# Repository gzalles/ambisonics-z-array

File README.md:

# MEMS Z-Array Mics

## [WIKI](https://github.com/gzalles/ambisonics-z-array/wiki)

A family of ambisonic microphones designed with MEMS capsules. These are affordable, easy-to-build arrays which can be used for multichannel audio recording (i.e., ambisonics).

Find an updated list of associated assets here:

1. m: Octave GNU code for plotting, analyzing and calibrating yourr own array
2. cad: various 3d objects you can print either online or at your university.
3. pcb: the files you need to make the pcbs or also you can have them made elsewhere.
4. svg: laser cutting files
5. conf: configuration files for kronlachner's convolution plug-in and filters
6. json: encoder presets for IEM MatrixMultiplier
7. wiki: instructions to build arrays

[AES Paper 1](https://www.researchgate.net/publication/320188555_A_Low-Cost_High-Quality_MEMS_Ambisonic_Microphone)

[AES Paper 2](https://www.researchgate.net/publication/338123588_Effects_of_Capsule_Coincidence_in_FOA_using_MEMS_Objective_Experiment)

<!-- TODO: move links to site.
 -->

## Pictures

<p align="center">
  
  <figcaption>

BigSpHEAR by FLL (working on a permutation).

## Contributing

Feel free to fork and request merge if you are interested in the project. Email to gzalles at ucsd dot edu.

## Authors

* [**Gabriel Zalles Ballivian**](http://gabrielzalles.com/)

## License

This project is licensed under the MIT License - see the [LICENSE.md](LICENSE.md) file for details

## Acknowledgments

* Charles Middlicott
* Charlie Mydlarz
* Agnieszka Roginska
* Julian Vanesse
* Andrea Genovese
* Braxton Boren
* Fernando Lopez-Lezcano
* Julius O Smith
* Alex Tung (Qualcomm)
* Raimundi Gonzalez (MSMA)
* Spencer Capiello (NYU)

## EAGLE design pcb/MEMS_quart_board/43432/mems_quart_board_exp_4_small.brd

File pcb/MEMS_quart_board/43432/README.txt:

43432 I2S Mic 

[VDD from J3 pin 2 on MCH]

LEFT and RIGHT PCBs (separate)

Left = CH1
Right = Ch2

Left tied to GRN (SEL)
Right tied to VDD (SEL)

MCH
///

BCLK > SCK 
LRCLK > WS 

Each data line has 2 channels. 
//////////////////////////////
J1 #2 input = channels 1/2
J1 #4 input = channels 3/4
etc.

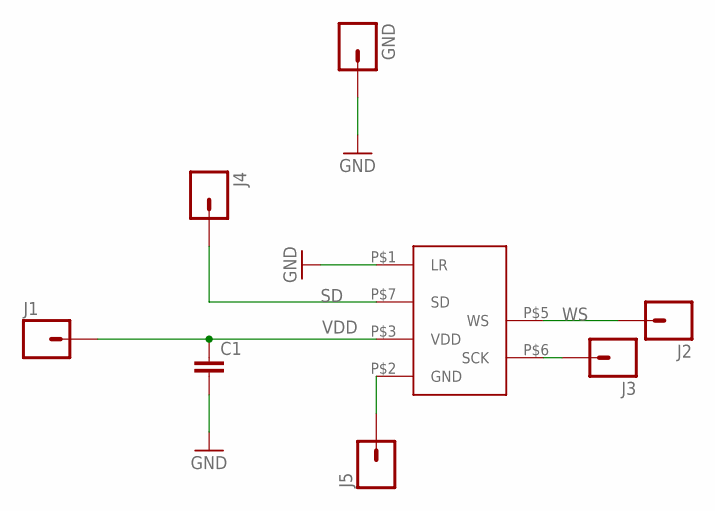
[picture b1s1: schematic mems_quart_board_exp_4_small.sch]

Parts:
C1: 0.1UF-16V(+-10%)(0402); 0402-CAP
GND: M01PTH_NO_SILK_YES_STOP; 1X01_NO_SILK
J1, J2, J3, J4, J5: M01NOSILK-KIT; 1X01NS-KIT
U$1: MEMS_ICS_43432

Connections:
GND: C1.2, GND.1, J5.1, U$1.P$1 (LR), U$1.P$2 (GND)
SCK: J3.1, U$1.P$6 (SCK)
SD: J4.1, U$1.P$7 (SD)
VDD: C1.1, J1.1, U$1.P$3 (VDD)
WS: J2.1, U$1.P$5 (WS)

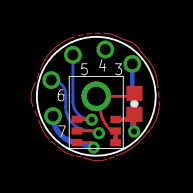
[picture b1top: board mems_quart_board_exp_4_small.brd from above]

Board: 2 copper layers, 6.6 x 6.6 mm, 8 parts (0 on the bottom side), 5 nets.

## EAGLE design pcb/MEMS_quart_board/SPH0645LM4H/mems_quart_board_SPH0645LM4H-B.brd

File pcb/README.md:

# PCB Files

* 3_175mmRadius: panelized files (can also be found in zip format)
* mems_quart_board_ics_40720.brd : single PCB for editing if needed.

These are the panelized files for the ICS-40720 board that Charlie Mydlarz designed. The radius of the board is 3.175mm. These are the current boards we are using for the analog mems FOA mic. I also added the original without panelizing.

There is a lot of information of the datasheet online regarding these capsules. In order to acquire these board one must find a PCB manufacturer and pay them to send you the boards.

In our current design we opt for 1mm thickness.

We use 2-sided PCBs.

If you need the dimensions of the board you can use: http://www.gerber-viewer.com/

The only thing they ask is to upload the zipped file. I have added the zipped file for your convenience since all sites as for it this way.

You might also want to get a stencil. With it you can more easily apply the paste to you PCBs.

credit: charlie mydlarz.

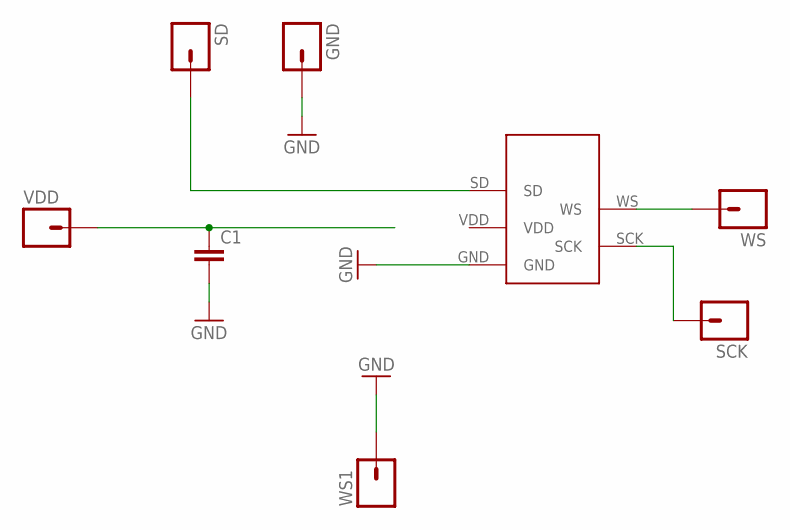
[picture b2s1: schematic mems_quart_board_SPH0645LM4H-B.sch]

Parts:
C1: 0.1UF-16V(+-10%)(0402); 0402-CAP
GND: M01PTH_NO_SILK_YES_STOP; 1X01_NO_SILK
SCK: M01NOSILK-KIT; 1X01NS-KIT
SD: M01NOSILK-KIT; 1X01NS-KIT
U$2: MEM_SPH0645LM4H-B; MEMS_SPH0645LM4H-B
VDD: M01NOSILK-KIT; 1X01NS-KIT
WS, WS1: M01NOSILK-KIT; 1X01NS-KIT

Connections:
GND: C1.2, GND.1, U$2.GND, WS1.1
unnamed: SCK.1, U$2.SCK
unnamed: SD.1, U$2.SD
unnamed: U$2.WS, WS.1
VDD: C1.1, U$2.VDD, VDD.1

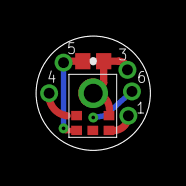
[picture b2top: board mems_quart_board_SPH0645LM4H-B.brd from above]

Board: 2 copper layers, 6.3 x 6.3 mm, 8 parts (0 on the bottom side), 5 nets.

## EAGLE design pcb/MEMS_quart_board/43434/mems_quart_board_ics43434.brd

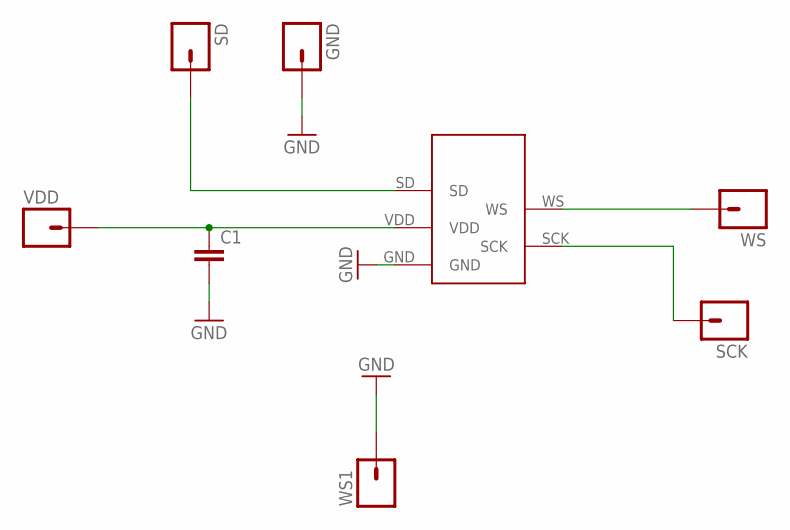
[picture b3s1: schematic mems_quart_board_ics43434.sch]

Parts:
C1: 0.1UF-16V(+-10%)(0402); 0402-CAP
GND: M01PTH_NO_SILK_YES_STOP; 1X01_NO_SILK
SCK: M01NOSILK-KIT; 1X01NS-KIT
SD: M01NOSILK-KIT; 1X01NS-KIT
U$1: MEM_ICS_43434; MEMS_ICS_43434
VDD: M01NOSILK-KIT; 1X01NS-KIT
WS, WS1: M01NOSILK-KIT; 1X01NS-KIT

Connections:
GND: C1.2, GND.1, U$1.GND, WS1.1
unnamed: SCK.1, U$1.SCK
unnamed: SD.1, U$1.SD
unnamed: U$1.WS, WS.1
VDD: C1.1, U$1.VDD, VDD.1

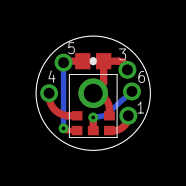
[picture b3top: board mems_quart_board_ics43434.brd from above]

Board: 2 copper layers, 6.3 x 6.3 mm, 8 parts (0 on the bottom side), 5 nets.

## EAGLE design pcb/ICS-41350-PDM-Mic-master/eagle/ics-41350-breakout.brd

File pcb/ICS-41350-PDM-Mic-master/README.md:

# ICS-41350-PDM-Mic
Open Source pcb layout and design for InvenSense ICS-41350 PDM Mic

# Datasheet
https://www.invensense.com/wp-content/uploads/2016/02/DS-000047-ICS-41350-v1.1.pdf

# Order PCBs
https://oshpark.com/shared_projects/o22Ddhzi

# Order ICS-41350
https://www.digikey.ca/product-detail/en/tdk-invensense/ICS-41350/1428-1064-1-ND/6025660

You'll also need a 0805 10uF and a 0603 .1uF smd capacitors and a 0603 10K Resistor.

# Front and Back PCB Preview

>The arrow points to where the hole for the mic goes.

>Bridge the S and G pad before using and bridge all three (S, G, V) if using module as RIGHT for stereo.

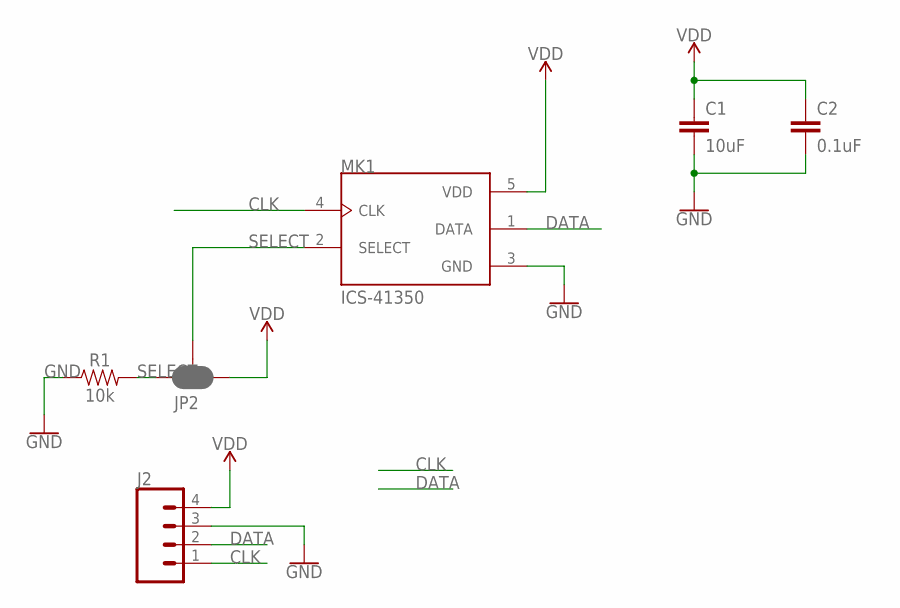
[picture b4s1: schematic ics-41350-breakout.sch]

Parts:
C1: 10uF; 0805
C2: 0.1uF; 0603
J2: CONN_041X04_NO_SILK; 1X04_NO_SILK
JP2: JUMPER-SMT_3_2-NC_PASTE_SILK; SMT-JUMPER_3_2-NC_PASTE_SILK
MK1: ICS-41350; MIC_ICS-41350
R1: 10k; 0603

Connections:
CLK: J2.1, MK1.4 (CLK)
DATA: J2.2, MK1.1 (DATA)
GND: C1.2, C2.2, J2.3, MK1.3 (GND), R1.1
SELECT: JP2.2, JP2.3, MK1.2 (SELECT), R1.2
VDD: C1.1, C2.1, J2.4, JP2.1, MK1.5 (VDD)

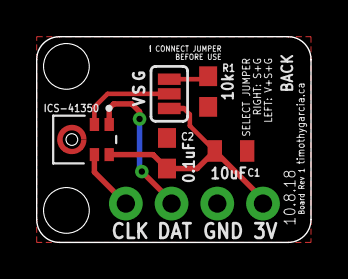
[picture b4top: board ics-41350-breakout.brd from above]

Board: 2 copper layers, 15.2 x 11.4 mm, 6 parts (0 on the bottom side), 5 nets.

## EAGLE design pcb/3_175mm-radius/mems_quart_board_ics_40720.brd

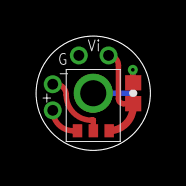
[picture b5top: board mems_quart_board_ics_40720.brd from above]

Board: 2 copper layers, 6.3 x 6.3 mm, 7 parts (0 on the bottom side), 4 nets.

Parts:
C1: 0402-CAP
GND: 1X01_NO_SILK
GND_IN: 1X01NS-KIT
U$1: MEMS_ICS_40720
VDD: 1X01NS-KIT
VOUT+: 1X01NS-KIT
VOUT-: 1X01NS-KIT

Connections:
GND: C1.2, GND.1, GND_IN.1, U$1.GND
VDD: C1.1, U$1.VDD, VDD.1
VOUT+: U$1.VOUT+, VOUT+.1
VOUT-: U$1.VOUT-, VOUT-.1

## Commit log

2019-04-18 push docs folder, try making site
2019-04-18 Set theme jekyll-theme-slate
2019-04-18 testing jekyll sites from doc folder
2019-04-18 read me and site, both readmes can be the same, but you have to do it manualy...
2019-04-19 Set theme jekyll-theme-cayman
2019-04-19 remove doc folder, oops
2019-04-19 added stuff from gsite and now have site building from amin branch (rather than docs)
2019-04-29 update materials on readme
2019-05-01 more added to the materials section
2019-05-01 testing pages
2019-05-01 still testing pages, relative path?
2019-05-01 push page 2
2019-05-01 testing page2 1:27
2019-05-03 push image 1
2019-05-03 this is a message
2019-05-03 from relative path to the other kind
    what is the other one?
2019-05-03 case sensitive
2019-05-03 commit for safety
2019-05-03 not sure what this is but it is bothering me so whatver
2019-05-03 back to relative with string uper case
2019-05-03 arrows on pic and stuff
2019-05-03 weird
2019-05-03 bob with arrow
2019-05-03 commit new image
2019-05-03 align the image? smaller?
2019-05-03 resize the other way
2019-05-03 old image is new
2019-05-03 get rid of old bob with arrows. DS_store thing?
2019-05-03 using % now for image size, better
2019-05-03 more materials links etc.
2019-05-03 little discrepancy fix with list
2019-05-03 problem persists
2019-05-04 matlab readme
2019-05-04 pushing readme modifications and gerzon filter. also stepper test. I want to write on the paper the methodology I used for getting my impulse response measurements. it would also be a goog idea to se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
2019-05-04 more instructions and links in the materials
2019-05-04 for some reason the image did not get uploaded...
2019-05-04 list numbering bug fix attempt
2019-05-04 bug list numbering fix 2
2019-05-04 how does the new pic look online?
2019-05-04 zipped gerber files, panelized
2019-05-05 the obj files looked all blurry stl seem to be better
2019-05-05 image to cad folder and a bit of info on the alligator mic clip;
2019-05-05 push the image itself
2019-05-05 link to paper and other details
2019-05-05 path change on cad image
2019-05-05 testing pages cad folder link?
2019-05-05 the pages thing worked!
2019-08-29 update gitignore
2019-08-29 wiki added
2019-08-29 wiki recursion avoided
2020-01-15 reset
2020-01-15 moving images to the wiki
2020-01-15 move img to wiki, master bracnh
2020-01-15 new readme, moved everything to wiki
2020-01-16 processing
2020-01-16 add audio and mat folder
2020-06-26 ud rm
2020-10-08 links to papers via researchgate
    🎤
2020-10-08 formatting issue
    is it fixed?
2020-10-08 i think this works
2020-10-29 udrm
2020-10-29 udrm
    all caps on jpg
2020-10-29 jpg lower case
2020-10-29 mmmm
2020-10-29 raw?
2020-10-29 change pic
2020-10-31 website fix?
2020-10-31 no !
2023-04-07 I hope this works
2023-04-07 readme
2023-04-07 icosa
2023-04-19 sparta filters
    can be used with sparta convolver
2023-04-19 organizing and removing old things
2023-04-19 upload filters
2023-05-11 Update README.md
    add wiki link to RM
2023-05-11 Update README.md
    change strings for paper links
2023-05-11 Update README.md
    add full names of contributors
2023-05-23 various
    svgs for laser cut concept, some more STLs, scanIR
2023-06-14 added templates for RPP
2023-06-14 Revert "added templates for RPP" This reverts commit ec4b30c20bdef6908c59d66a3255f2a0dc4f4689.
2023-06-14 rpp templates
2023-06-15 Revert "added templates for RPP" This reverts commit ec4b30c20bdef6908c59d66a3255f2a0dc4f4689. Again.
2023-06-15 add templates
2023-08-31 Update README.md
    The wiki string was too small
2023-08-31 Update README.md
    Clarification
2023-09-01 we still have work to do
    the repos messy :(
2023-09-01 test
    nothing to see here.
2023-09-01 again
    lol
2023-09-01 ignore
2023-09-01 boo
    yah

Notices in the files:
parts and their libraries:
SparkFun-Capacitors: Licensing: Creative Commons ShareAlike 4.0 International - https://creativecommons.org/licenses/by-sa/4.0
